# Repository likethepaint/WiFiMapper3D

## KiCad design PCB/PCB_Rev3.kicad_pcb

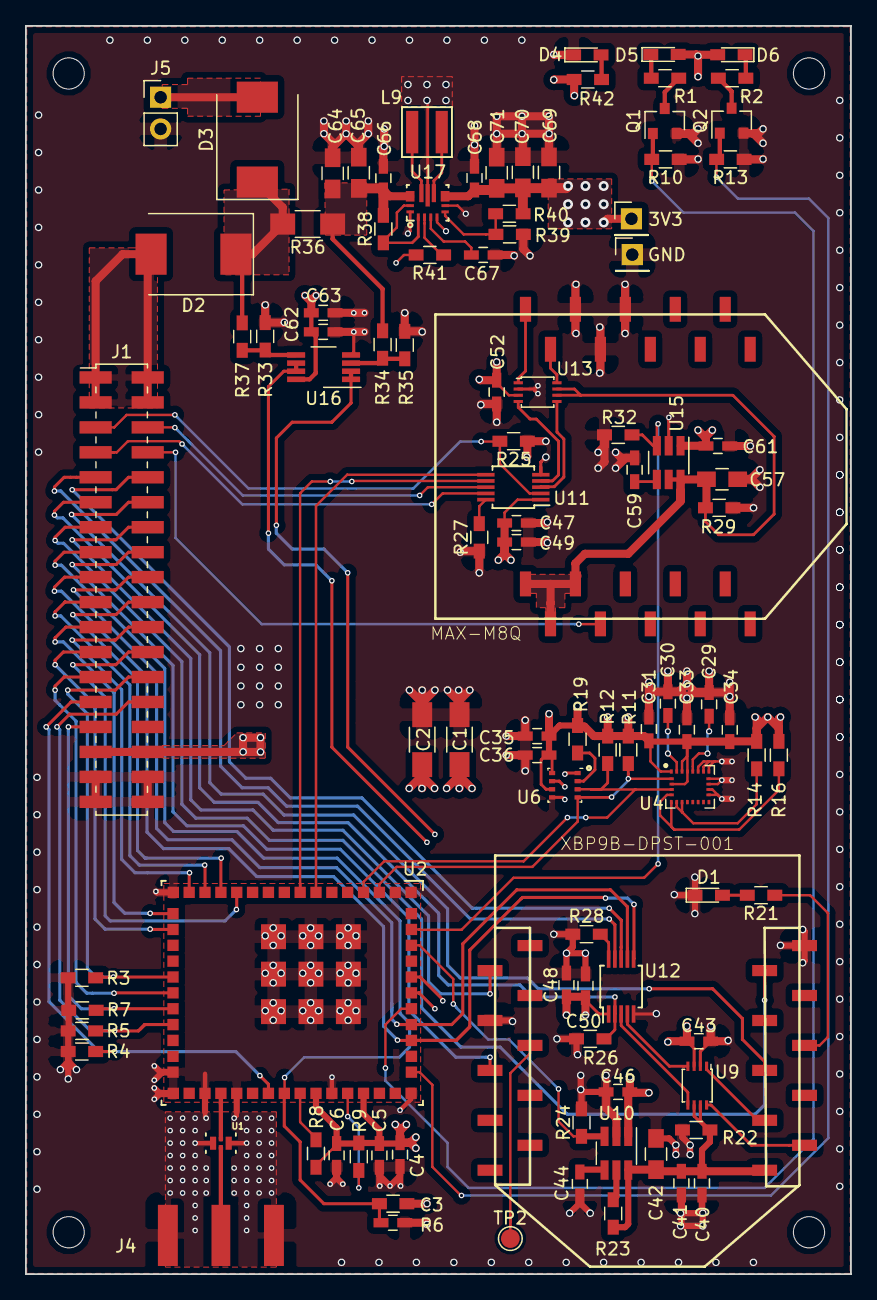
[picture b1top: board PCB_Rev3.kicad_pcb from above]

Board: 4 copper layers, 66.1 x 100.0 mm, 102 parts (0 on the bottom side), 81 nets.

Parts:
3V3: Pin_Header_Straight_1x01_Pitch2.54mm
C1, C2: 100uF; C_1206_HandSoldering
C3, C4, C5, C6, C30, C31, C33, C36, C43, C49, C50, C52, C67: 0.1uF; C_0603_HandSoldering
C29, C40, C62, C63: 0.01uF; C_0603_HandSoldering
C34, C41, C66, C68: 10uF; C_0603_HandSoldering
C35, C47, C48: 4.7uF; C_0603_HandSoldering
C42, C57, C69, C70, C71: 22uF; C_0805_HandSoldering
C44, C59: 0.001uF; C_0603_HandSoldering
C46, C61: 1uF; C_0603_HandSoldering
C64, C65: 10uF; C_0805_HandSoldering
D1, D4: LG L29K-F2J1-24-Z; LED_0603_HandSoldering
D2, D3: D; D_SMC
D5, D6: LED; LED_0603_HandSoldering
GND: Pin_Header_Straight_1x01_Pitch2.54mm
J1: Conn_02x18_Odd_Even; Pin_Header_Straight_2x18_Pitch2.00mm_SMD
J4: WIFI SMA; Amphenol-132289rp
J5: Conn_01x02; Pin_Header_Straight_1x02_Pitch2.54mm
L9: 1.5uH; XFL4020-152ME
Q1, Q2: BSS138; SOT-23
R1, R2: 270; R_0603_HandSoldering
R3, R4, R5, R7, R10, R13, R41: 100k; R_0603_HandSoldering
R6, R14, R16, R25, R26, R27, R28, R38: 10k; R_0603_HandSoldering
R8, R9: DNP; R_0603_HandSoldering
R11, R12: 4.7k; R_0603_HandSoldering
R19, R22, R24, R29, R32: 100K; R_0603_HandSoldering
R21, R42: 330; R_0603_HandSoldering
R23: 0; R_0603_HandSoldering
R33, R34, R35, R37: ???; R_0603_HandSoldering
R36: 0.05; R_1206_HandSoldering
R39: 150k; R_0603_HandSoldering
R40: 470k; R_0603_HandSoldering
TP2: Test_Point; Test_Point_Pad_d1.5mm
U1: DEA202450BT-1294C1-H
U2: CC3220MODSFMOB; CC3220MODSF12MOBR
U4: LSM9DS1; LGA-24L_3x3.5mm_Pitch0.43mm
U6: BMP280; Bosch_LGA-8_2.5x2.5mm_Pitch0.65mm_ClockwisePinNumbering
U8: XBP9B-DPST-001; XBEE_SMD
U9, U13: TXB0102DCU; VSSOP-8_2.4x2.1mm_Pitch0.5mm
U10, U15: TPS22918; SOT-23-6_Handsoldering
U11, U12: FSUSB42MUX; MSOP-10_3x3mm_Pitch0.5mm
U14: MAX-M8Q; XBEE_SMD
U16: OPA2340; VSSOP-8_3.0x3.0mm_Pitch0.65mm
U17: TPS63070RNM; TPS63070RNMR

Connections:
+3V3: 3V3.1, C1.1, C2.1, C4.1, C5.1, C6.1, C31.1, C33.1, C34.1, C35.1, C36.1, C43.1, C46.2, C47.1, C48.1, C49.1, C50.1, C52.1, C61.2, C62.1, C63.1, C68.1, C69.1, C70.1, C71.1, D5.2, D6.2, J1.31, J1.32, R6.1, R8.2, R9.2, R11.1, R12.1, R14.1, R16.1, R19.2, R40.2, R41.2, R42.1, U2.37, U2.40, U4.1, U4.3, U4.22, U4.23, U6.6, U6.8, U9.3, U10.1, U11.1, U12.1, U13.3, U15.1, U16.8, U17.7, U17.8
/GPS/GPS_VCC: C57.1, R29.1, U13.6, U13.7, U14.11, U14.12, U14.13, U15.5, U15.6
/GPS/RX_ISOLATED: U13.1, U14.10
/GPS/TX_ISOLATED: U13.8, U14.9
/Page3/RX_ISOLATED: U8.3, U9.1
/Page3/TX_ISOLATED: U8.2, U9.8
/Page3/XBEE_VCC: C40.1, C41.1, C42.1, R22.1, R23.1, U8.1, U9.6, U9.7, U10.6
CC_ADC_CH2: U2.49, U16.1, U16.2
CC_ADC_CH3: U2.50, U16.6, U16.7
CC_GPIO7: R24.1, U2.52, U10.3
CC_GPIO8: R32.1, U2.53, U15.3
CC_SCL0: R11.2, U2.3, U4.2, U6.4
CC_SDA0: R12.2, U2.4, U4.4, U6.3
CC_UART0_RX: J1.18, U2.47, U12.7
CC_UART0_TX: J1.17, U2.46, U12.6
CC_UART1_RX: U2.8, U11.7
CC_UART1_TX: U2.7, U11.6
CC_nRESET: C3.1, J1.15, R6.2, U2.35
FLASH_CLK: J1.22, U2.15
FLASH_CS: J1.19, U2.14
FLASH_DIN: J1.20, U2.13
FLASH_DOUT: J1.21, U2.17
GND: C1.2, C2.2, C3.2, C4.2, C5.2, C6.2, C29.2, C30.2, C31.2, C33.2, C34.2, C35.2, C36.2, C40.2, C41.2, C42.2, C43.2, C44.2, C46.1, C47.2, C48.2, C49.2, C50.2, C52.2, C57.2, C59.2, C61.1, C62.2, C63.2, C64.2, C65.2, C66.2, C67.2, C68.2, C69.2, C70.2, C71.2, D1.1, D4.1, GND.1, J1.33, J1.34, J1.35, J1.36, J4.2, J5.2, Q1.2, Q2.2, R3.2, R4.2, R5.2, R7.2, R10.1, R13.1, R22.2, R24.2, R25.1, R26.1, R27.1, R28.1, R29.2, R32.2, R33.2, R35.1, R39.2, U1.2, U1.4, U2.1, U2.2, U2.16, U2.27, U2.28, U2.30, U2.32, U2.38, U2.43, U2.55, U2.56, U2.57, U2.58, U2.59, U2.60, U2.61, U2.62, U2.63, U4.14, U4.15, U4.16, U4.17, U4.18, U4.19, U4.20, U6.1, U6.5, U6.7, U8.10, U8.14, U9.2, U10.2, U11.5, U12.5, U13.2, U14.6, U14.7, U14.8, U15.2, U16.4, U17.4, U17.6, U17.10, U17.15
GPS_DEBUG_EN: J1.5, R25.2, U11.2
GPS_DEBUG_RX: J1.6, U11.8
GPS_DEBUG_TX: J1.7, U11.9
GPS_RESET_N: J1.8, U14.14
GPS_RX: U11.4, U13.4
GPS_TX: U11.3, U13.5
JTAG_TCK: J1.26, R3.1, U2.21
JTAG_TDI: J1.24, U2.12
JTAG_TDO: J1.23, U2.18
JTAG_TMS: J1.25, U2.22
unnamed: C29.1, U4.21
unnamed: C30.1, U4.24
unnamed: C44.1, U10.4
unnamed: C59.1, U15.4
unnamed: C64.1, C65.1, C66.1, R34.2, R36.1, R38.2, U17.12, U17.13
unnamed: C67.1, U17.3
unnamed: D1.2, R21.2
unnamed: D2.1, D3.1, R36.2, R37.2
unnamed: D4.2, R42.2
unnamed: D5.1, R1.2
unnamed: D6.1, R2.2
unnamed: J4.1, U1.3
unnamed: L9.1, U17.11
unnamed: L9.2, U17.9
unnamed: Q1.3, R1.1
unnamed: Q2.3, R2.1
unnamed: R8.1, U2.36
unnamed: R9.1, U2.39
unnamed: R14.2, U4.7, U4.8
unnamed: R16.2, U4.5, U4.6
unnamed: R19.1, U6.2
unnamed: R21.1, U8.6
unnamed: R23.2, U10.5
unnamed: R27.2, U11.10
unnamed: R28.2, U12.10
unnamed: R33.1, R37.1, U16.5
unnamed: R34.1, R35.2, U16.3
unnamed: R38.1, U17.1, U17.14
unnamed: R39.1, R40.1, U17.5
unnamed: R41.1, U17.2
unnamed: TP2.1, U8.15
unnamed: U1.1, U2.31
SOP0: J1.27, R4.1, U2.34
SOP1: J1.28, R5.1, U2.24
SOP2: J1.29, R7.1, U2.23
STATUS_LED_1: Q2.1, R13.2, U2.44
STATUS_LED_2: Q1.1, R10.2, U2.48
VBAT: D3.2, J5.1
VBUS: D2.2, J1.1, J1.2, J1.3, J1.4
XBEE_CTS: J1.14, U8.12
XBEE_DEBUG_EN: J1.11, R26.2, U12.2
XBEE_DEBUG_RX: J1.10, U12.8
XBEE_DEBUG_TX: J1.9, U12.9
XBEE_DTR: J1.13, U8.9
XBEE_RESET: J1.12, U8.5
XBEE_RTS: J1.16, U8.16
XBEE_RX: U9.4, U12.4
XBEE_TX: U9.5, U12.3

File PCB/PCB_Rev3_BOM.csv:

Reference Type, Quantity, Reference, Value, Footprint, Datasheet, Field4, Field5, Field6, Field7, Field8
C,2,"C44,C59,",0.001uF,Capacitors_SMD:C_0603_HandSoldering,,,,,,
C,4,"C29,C40,C62,C63,",0.01uF,Capacitors_SMD:C_0603_HandSoldering,,,,,,
C,13,"C3,C4,C5,C6,C30,C33,C31,C36,C43,C50,C49,C52,C67,",0.1uF,Capacitors_SMD:C_0603_HandSoldering,,,,,,
C,2,"C46,C61,",1uF,Capacitors_SMD:C_0603_HandSoldering,,,,,,
C,3,"C35,C48,C47,",4.7uF,Capacitors_SMD:C_0603_HandSoldering,,,,,,
C,6,"C34,C41,C64,C65,C66,C68,",10uF,Capacitors_SMD:C_0603_HandSoldering,,,,,,
C,5,"C42,C57,C69,C70,C71,",22uF,Capacitors_SMD:C_0805_HandSoldering,,,,,,
C,2,"C1,C2,",100uF,Capacitors_SMD:C_1206_HandSoldering,,,,,,
D,2,"D2,D3,",D,Diodes_SMD:D_SMC,VS-30BQ015-M3/9AT,,,,,
D,2,"D6,D5,",LED,LEDs:LED_0603_HandSoldering,,,,,,
D,2,"D1,D4,",LG L29K-F2J1-24-Z ,LEDs:LED_0603_HandSoldering,,,,,,
J,1,"J5,",Conn_01x02,Pin_Headers:Pin_Header_Straight_1x02_Pitch2.54mm,,,,,,
J,1,"J1,",Conn_02x18_Odd_Even,Pin_Headers:Pin_Header_Straight_2x18_Pitch2.00mm_SMD,,,,,,
J,1,"J4,",WIFI SMA,WiFiMapSpecific:Amphenol-132289rp,,,,,,
L,1,"L9,",1.5uH,WiFiMapSpecific:XFL4020-152ME,XFL4020-152ME,,,,,
Q,2,"Q2,Q1,",BSS138,TO_SOT_Packages_SMD:SOT-23,https://www.fairchildsemi.com/datasheets/BS/BSS138.pdf,,,,,
R,1,"R23,",0,Resistors_SMD:R_0603_HandSoldering,,,,,,
R,1,"R36,",0.05,Resistors_SMD:R_1206_HandSoldering,,,,,,
R,2,"R2,R1,",270,Resistors_SMD:R_0603_HandSoldering,,,,,,
R,2,"R21,R42,",330,Resistors_SMD:R_0603_HandSoldering,,,,,,
R,4,"R34,R35,R37,R33,",???,Resistors_SMD:R_0603_HandSoldering,,,,,,
R,2,"R8,R9,",DNP,Resistors_SMD:R_0603_HandSoldering,,,,,,
R,5,"R19,R24,R22,R29,R32,",100K,Resistors_SMD:R_0603_HandSoldering,,,,,,
R,2,"R11,R12,",4.7k,Resistors_SMD:R_0603_HandSoldering,,,,,,
R,8,"R6,R14,R16,R28,R26,R27,R25,R38,",10k,Resistors_SMD:R_0603_HandSoldering,,,,,,
R,7,"R4,R5,R7,R3,R13,R10,R41,",100k,Resistors_SMD:R_0603_HandSoldering,,,,,,
R,1,"R39,",150k,Resistors_SMD:R_0603_HandSoldering,,,,,,
R,1,"R40,",470k,Resistors_SMD:R_0603_HandSoldering,,,,,,
TP,1,"TP2,",Test_Point,Connectors_TestPoints:Test_Point_Pad_d1.5mm,,,,,,
U,1,"U6,",BMP280,Housings_LGA:Bosch_LGA-8_2.5x2.5mm_Pitch0.65mm_ClockwisePinNumbering,,,,,,
U,1,"U2,",CC3220MODSFMOB,WiFiMapSpecific:CC3220MODSF12MOBR,,,,,,
U,1,"U1,",DEA202450BT-1294C1-H,WiFiMapSpecific:DEA202450BT-1294C1-H,,,,,,
U,2,"U12,U11,",FSUSB42MUX,Housings_SSOP:MSOP-10_3x3mm_Pitch0.5mm,,,,,,
U,1,"U4,",LSM9DS1,Housings_LGA:LGA-24L_3x3.5mm_Pitch0.43mm,http://www.st.com/content/ccc/resource/technical/document/da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,,,,,
U,1,"U14,",MAX-M8Q,WiFiMapSpecific:XBEE_SMD,,,,,,
U,1,"U16,",OPA2340,Housings_SSOP:VSSOP-8_3.0x3.0mm_Pitch0.65mm,http://www.ti.com/lit/ds/symlink/opa4340.pdf,,,,,
U,2,"U10,U15,",TPS22918,TO_SOT_Packages_SMD:SOT-23-6_Handsoldering,,,,,,
U,1,"U17,",TPS63070RNM,WiFiMapSpecific:TPS63070RNMR,,,,,,
U,2,"U9,U13,",TXB0102DCU,Housings_SSOP:VSSOP-8_2.4x2.1mm_Pitch0.5mm,http://www.ti.com/lit/ds/symlink/txb0102.pdf,,,,,
U,1,"U8,",XBP9B-DPST-001,WiFiMapSpecific:XBEE_SMD,Digi International,"XBee-PRO 900HP _S3B_ Point2Multipoint, 900MHz, 250mW, RPSMA, 10Kbps",38.27 USD,XBP9B-DPST-001,Module Digi International,Warning

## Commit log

2018-12-13 Added MATLAB and CCS
2018-12-13 Added massive COSMOS files'
2018-12-13 Remove COSMOS
2018-12-13 Added cosmos template
2018-12-13 Added kicad files

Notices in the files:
parts and their libraries:
Copyright 2016 Accelerated Designs. All rights reserved.
